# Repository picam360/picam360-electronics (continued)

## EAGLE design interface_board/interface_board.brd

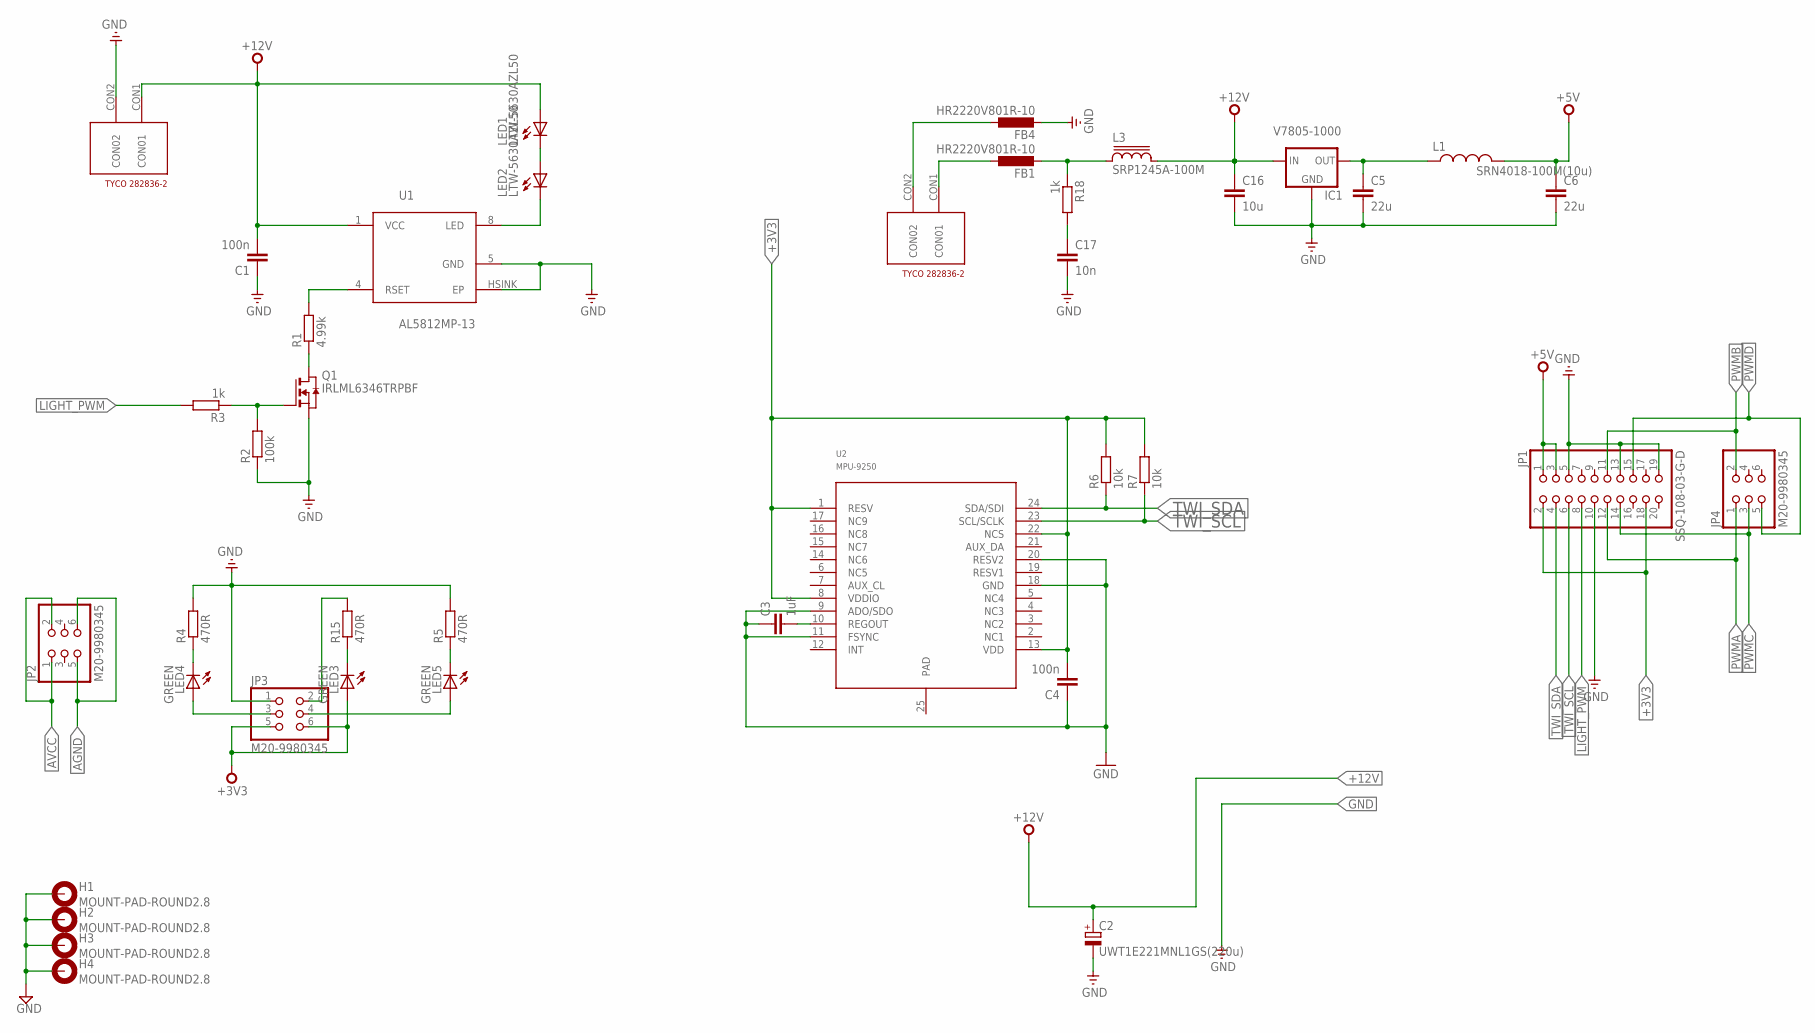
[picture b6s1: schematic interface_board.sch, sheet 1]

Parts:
C1, C4: 100n; C0402
C2: UWT1E221MNL1GS(220u); 153CLV-0810
C3: 1uF; C0402
C5, C6: 22u; C0603
C16: 10u; C0603
C17: 10n; C0402
FB1, FB4: HR2220V801R-10; L5650M
H1, H2, H3, H4: MOUNT-PAD-ROUND2.8; 2,8-PAD
IC1: V7805-1000; DIP_3PIN
JP1: SSQ-108-03-G-D; 2X10
JP2, JP3, JP4: M20-9980345; 2X03
L1: SRN4018-100M(10u); BOURNS-SRN4018
L3: SRP1245A-100M; SRP1250A
LED1, LED2: LTW-5630AZL50; LITEON-5630
LED3, LED4, LED5: GREEN; CHIP-LED0603
Q1: IRLML6346TRPBF; SOT23
R1: 4.99k; R0402
R2: 100k; R0402
R3, R18: 1k; R0402
R4, R5, R15: 470R; R0402
R6, R7: 10k; R0402
U1: AL5812MP-13; MSOP-8EP
U2: MPU-9250; LEAD-QFN24
U$2, U$4: 282836-2

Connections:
+3V3: C4.2, JP1.2, JP1.18, JP3.5, JP3.6, LED3.A, R6.2, R7.2, U2.1 (RESV), U2.8 (VDDIO), U2.13 (VDD), U2.22 (NCS); also elsewhere on the board
+5V: C6.1, JP1.1, JP1.3, L1.P$1 (1); also elsewhere on the board
+12V: C1.2, C2.+, C16.1, IC1.IN, L3.2, LED1.A1 (A), LED1.A2 (A), LED1.A3 (A), U1.1 (VCC), U$4.CON1 (CON01)
AGND: FB4.1, JP2.5, JP2.6, U$2.CON2 (CON02)
AVCC: FB1.1, JP2.1, JP2.2, U$2.CON1 (CON01)
GND: C1.1, C2.-, C3.1, C4.1, C5.2, C6.2, C16.2, C17.2, FB4.2, H1.B2,8, H2.B2,8, H3.B2,8, H4.B2,8, IC1.GND, JP1.5, JP1.10, JP1.13, JP1.19, JP3.1, Q1.2 (S), R2.1, R4.2, R5.2, U1.5 (GND), U1.HSINK (EP), U2.9 (ADO/SDO), U2.11 (FSYNC), U2.18 (GND), U2.20 (RESV2), U$4.CON2 (CON02); also elsewhere on the board
LIGHT_PWM: JP1.8, R3.2
unnamed: LED1.C1 (C), LED1.C2 (C), LED2.A1 (A), LED2.A2 (A), LED2.A3 (A)
unnamed: LED4.C, R4.1
unnamed: FB1.2, L3.1, R18.1
unnamed: C3.2, U2.10 (REGOUT)
unnamed: R1.2, U1.4 (RSET)
unnamed: Q1.3 (D), R1.1
unnamed: Q1.1 (G), R2.2, R3.1
unnamed: JP3.3, LED4.A
unnamed: LED2.C1 (C), LED2.C2 (C), U1.8 (LED)
unnamed: C5.1, IC1.OUT, L1.P$2 (2)
unnamed: JP3.4, LED5.A
unnamed: LED5.C, R5.1
unnamed: JP3.2, R15.2
unnamed: LED3.C, R15.1
unnamed: C17.1, R18.2
PWMA: JP1.12, JP4.1
PWMB: JP1.11, JP4.2
PWMC: JP1.14, JP4.3
PWMD: JP1.15, JP4.5
TWI_SCL: JP1.6, R7.1, U2.23 (SCL/SCLK)
TWI_SDA: JP1.4, R6.1, U2.24 (SDA/SDI)

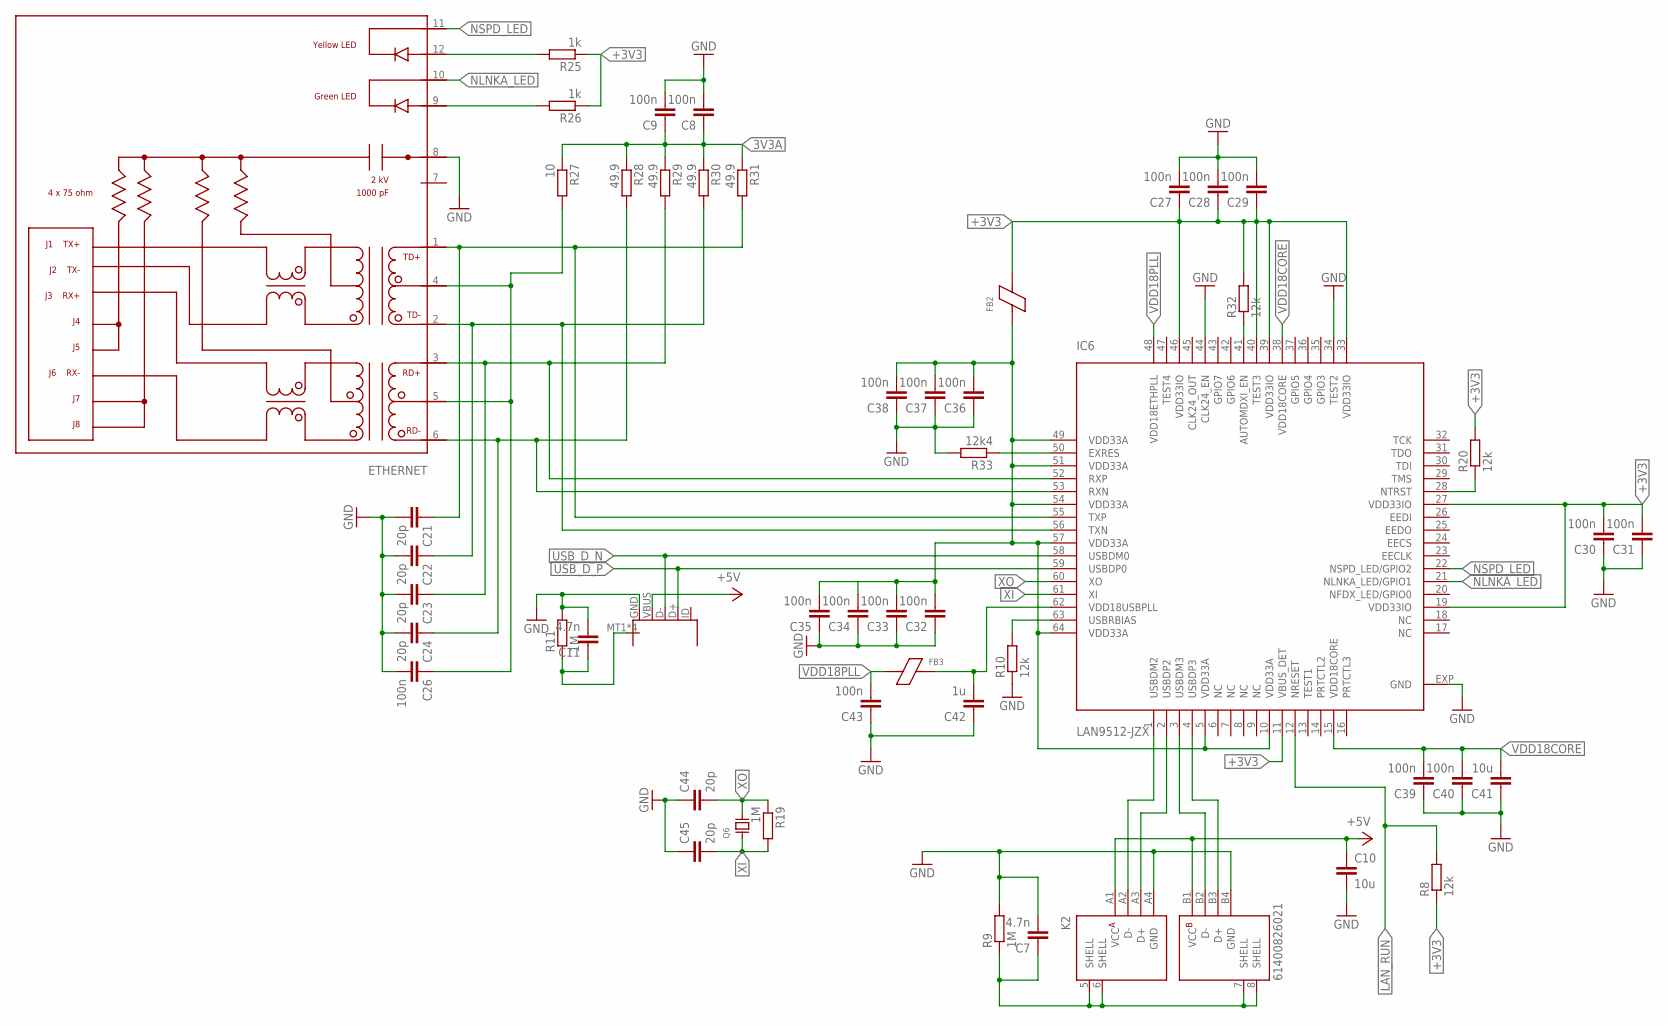
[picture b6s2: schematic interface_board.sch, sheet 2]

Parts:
C7, C11: 4.7n; C0402
C8, C9, C26, C27, C28, C29, C30, C31, C32, C33, C34, C35, C36, C37, C38, C39, C40, C43: 100n; C0402
C10, C41: 10u; C0603
C21, C22, C23, C24, C44, C45: 20p; C0402
C42: 1u; C0402
ETHERNET: HR911105A; RJ45
FB2, FB3: 742792022; C0805
IC6: LAN9512-JZX; QFN64-9X9
JP6: 10118192-0001LF; USB-MICRO
K2: 61400826021
Q6: FA-238 25.0000MB; CTS_32X25
R8, R10, R20, R32: 12k; R0402
R9, R11, R19: 1M; R0402
R25, R26: 1k; R0402
R27: 10; R0402
R28, R29, R30, R31: 49.9; R0402
R33: 12k4; R0402

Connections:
3V3A: C8.1, C9.1, C32.2, C33.2, C34.2, C35.2, C36.2, C37.2, C38.2, FB2.1, IC6.5 (VDD33A), IC6.10 (VDD33A), IC6.49 (VDD33A), IC6.51 (VDD33A), IC6.54 (VDD33A), IC6.57 (VDD33A), IC6.64 (VDD33A), R27.1, R28.1, R29.1, R30.1, R31.1
+3V3: C27.1, C28.1, C29.1, C30.2, C31.2, FB2.2, IC6.11 (VBUS_DET), IC6.19 (VDD33IO), IC6.27 (VDD33IO), IC6.33 (VDD33IO), IC6.39 (VDD33IO), IC6.40 (TEST3), IC6.46 (VDD33IO), R8.1, R20.2, R25.1, R26.1, R32.2; also elsewhere on the board
+5V: C10.1, JP6.VBUS, K2.A1 (VCC), K2.B1 (VCC); also elsewhere on the board
AVDD18PLL: C42.2, FB3.2, IC6.62 (VDD18USBPLL)
GND: C7.2, C8.2, C9.2, C10.2, C11.2, C21.2, C22.2, C23.2, C24.2, C26.2, C27.2, C28.2, C29.2, C30.1, C31.1, C32.1, C33.1, C34.1, C35.1, C36.1, C37.1, C38.1, C39.1, C40.1, C41.1, C42.1, C43.1, C44.1, C45.1, ETHERNET.8, IC6.34 (TEST2), IC6.44 (CLK24_EN), IC6.EXP (GND), JP6.GND, K2.A4 (GND), K2.B4 (GND), R9.2, R10.1, R11.2, R33.2; also elsewhere on the board
LAN_RUN: IC6.12 (NRESET), R8.2
unnamed: ETHERNET.12, R25.2
unnamed: ETHERNET.9, R26.2
unnamed: C26.1, ETHERNET.4, ETHERNET.5, R27.2
unnamed: IC6.63 (USBRBIAS), R10.2
unnamed: IC6.41 (AUTOMDXI_EN), R32.1
unnamed: IC6.50 (EXRES), R33.1
unnamed: IC6.28 (NTRST), R20.1
NLNKA_LED: ETHERNET.10, IC6.21 (NLNKA_LED/GPIO1)
NSPD_LED: ETHERNET.11, IC6.22 (NSPD_LED/GPIO2)
RX_N: C24.1, ETHERNET.6, IC6.53 (RXN), R28.2
RX_P: C23.1, ETHERNET.3, IC6.52 (RXP), R29.2
TX_N: C22.1, ETHERNET.2, IC6.56 (TXN), R30.2
TX_P: C21.1, ETHERNET.1, IC6.55 (TXP), R31.2
USB1_SHELL: C7.1, K2.5 (SHELL), K2.6 (SHELL), K2.7 (SHELL), K2.8 (SHELL), R9.1
USB2_SHELL: C11.1, JP6.MT1 (SHELL), JP6.MT2 (SHELL), JP6.P$1 (SHELL), JP6.P$2 (SHELL), R11.1
USBD2_N: IC6.1 (USBDM2), K2.A2 (D-)
USBD2_P: IC6.2 (USBDP2), K2.A3 (D+)
USBD3_N: IC6.3 (USBDM3), K2.B2 (D-)
USBD3_P: IC6.4 (USBDP3), K2.B3 (D+)
USB_D_N: IC6.58 (USBDM0), JP6.D-
USB_D_P: IC6.59 (USBDP0), JP6.D+
VDD18CORE: C39.2, C40.2, C41.2, IC6.15 (VDD18CORE), IC6.38 (VDD18CORE)
VDD18PLL: C43.2, FB3.1, IC6.48 (VDD18ETHPLL)
XI: C45.2, IC6.61 (XI), Q6.1 (X1), R19.2
XO: C44.2, IC6.60 (XO), Q6.3 (X2), R19.1

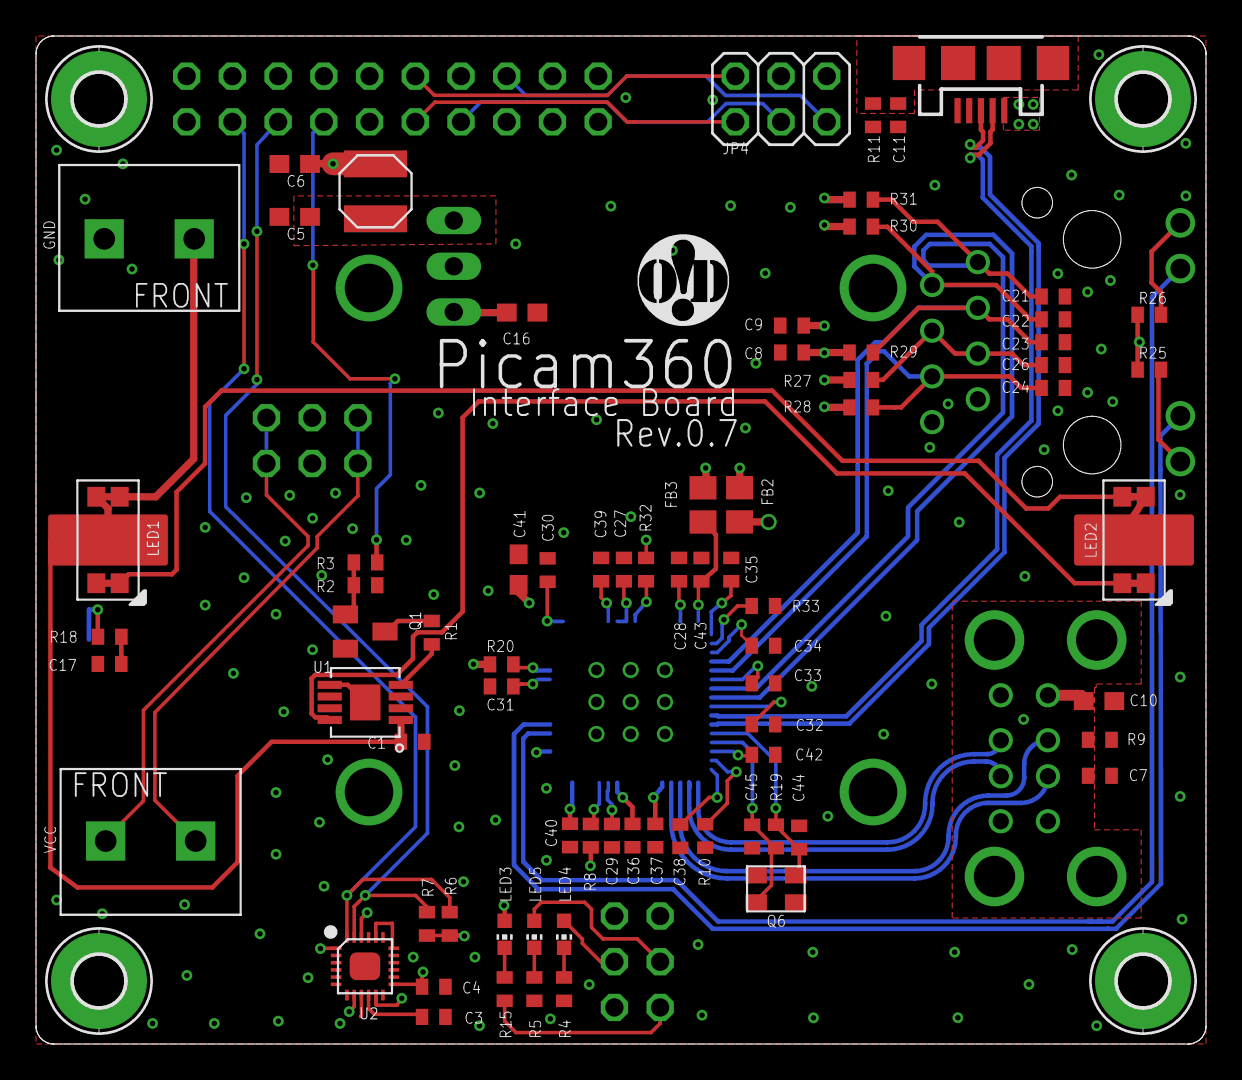
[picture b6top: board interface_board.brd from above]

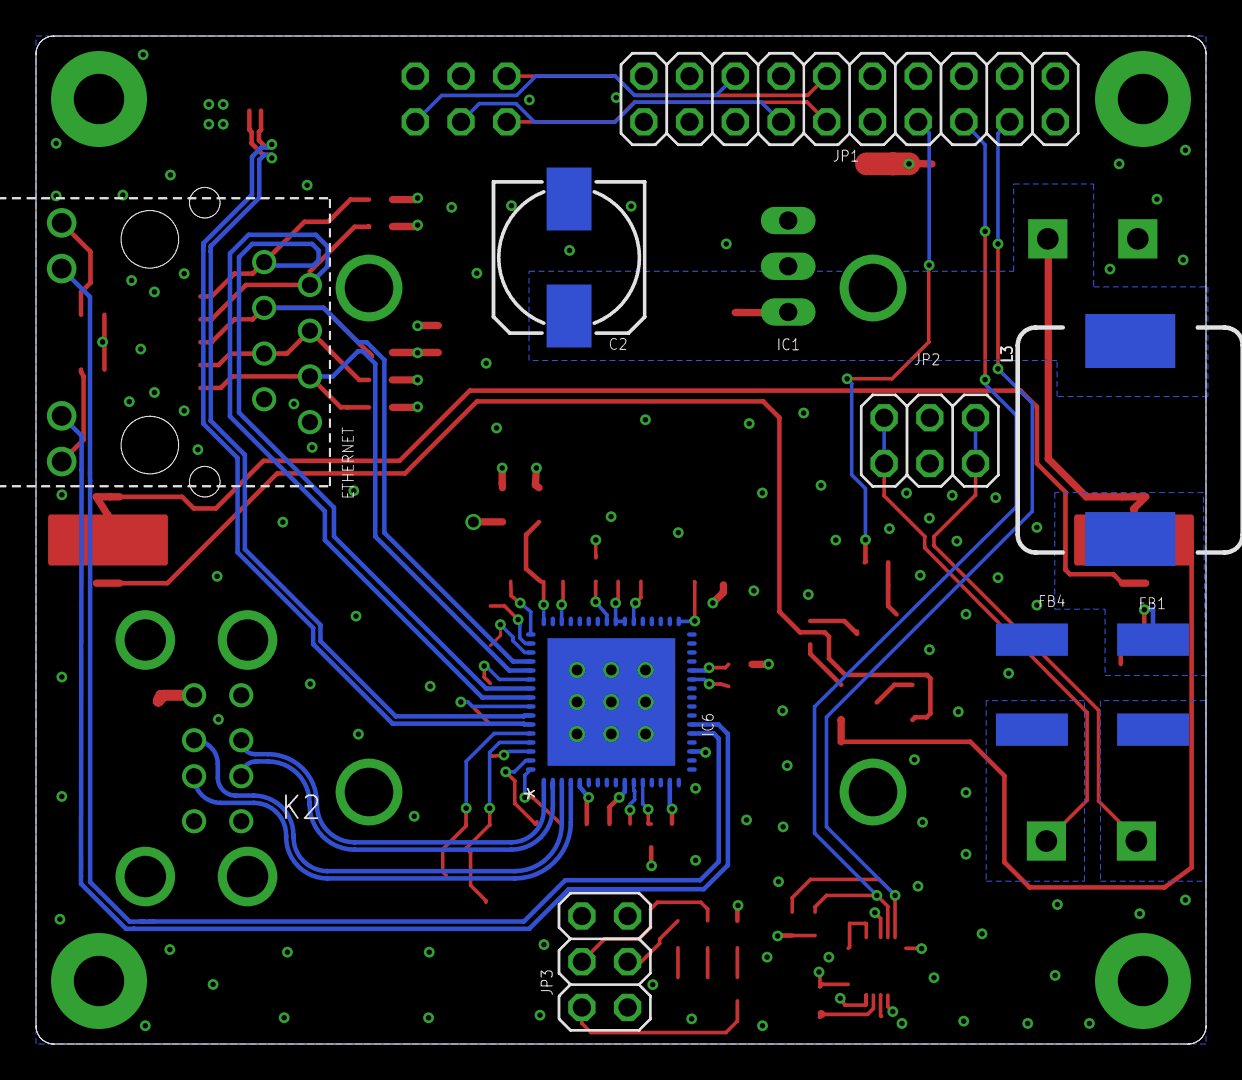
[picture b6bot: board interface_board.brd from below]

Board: 4 copper layers, 65.0 x 56.0 mm, 93 parts (12 on the bottom side), 56 nets.

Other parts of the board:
LOGO1: OHMYDIGIFAB_LOGO
U$1: TENDA_P200

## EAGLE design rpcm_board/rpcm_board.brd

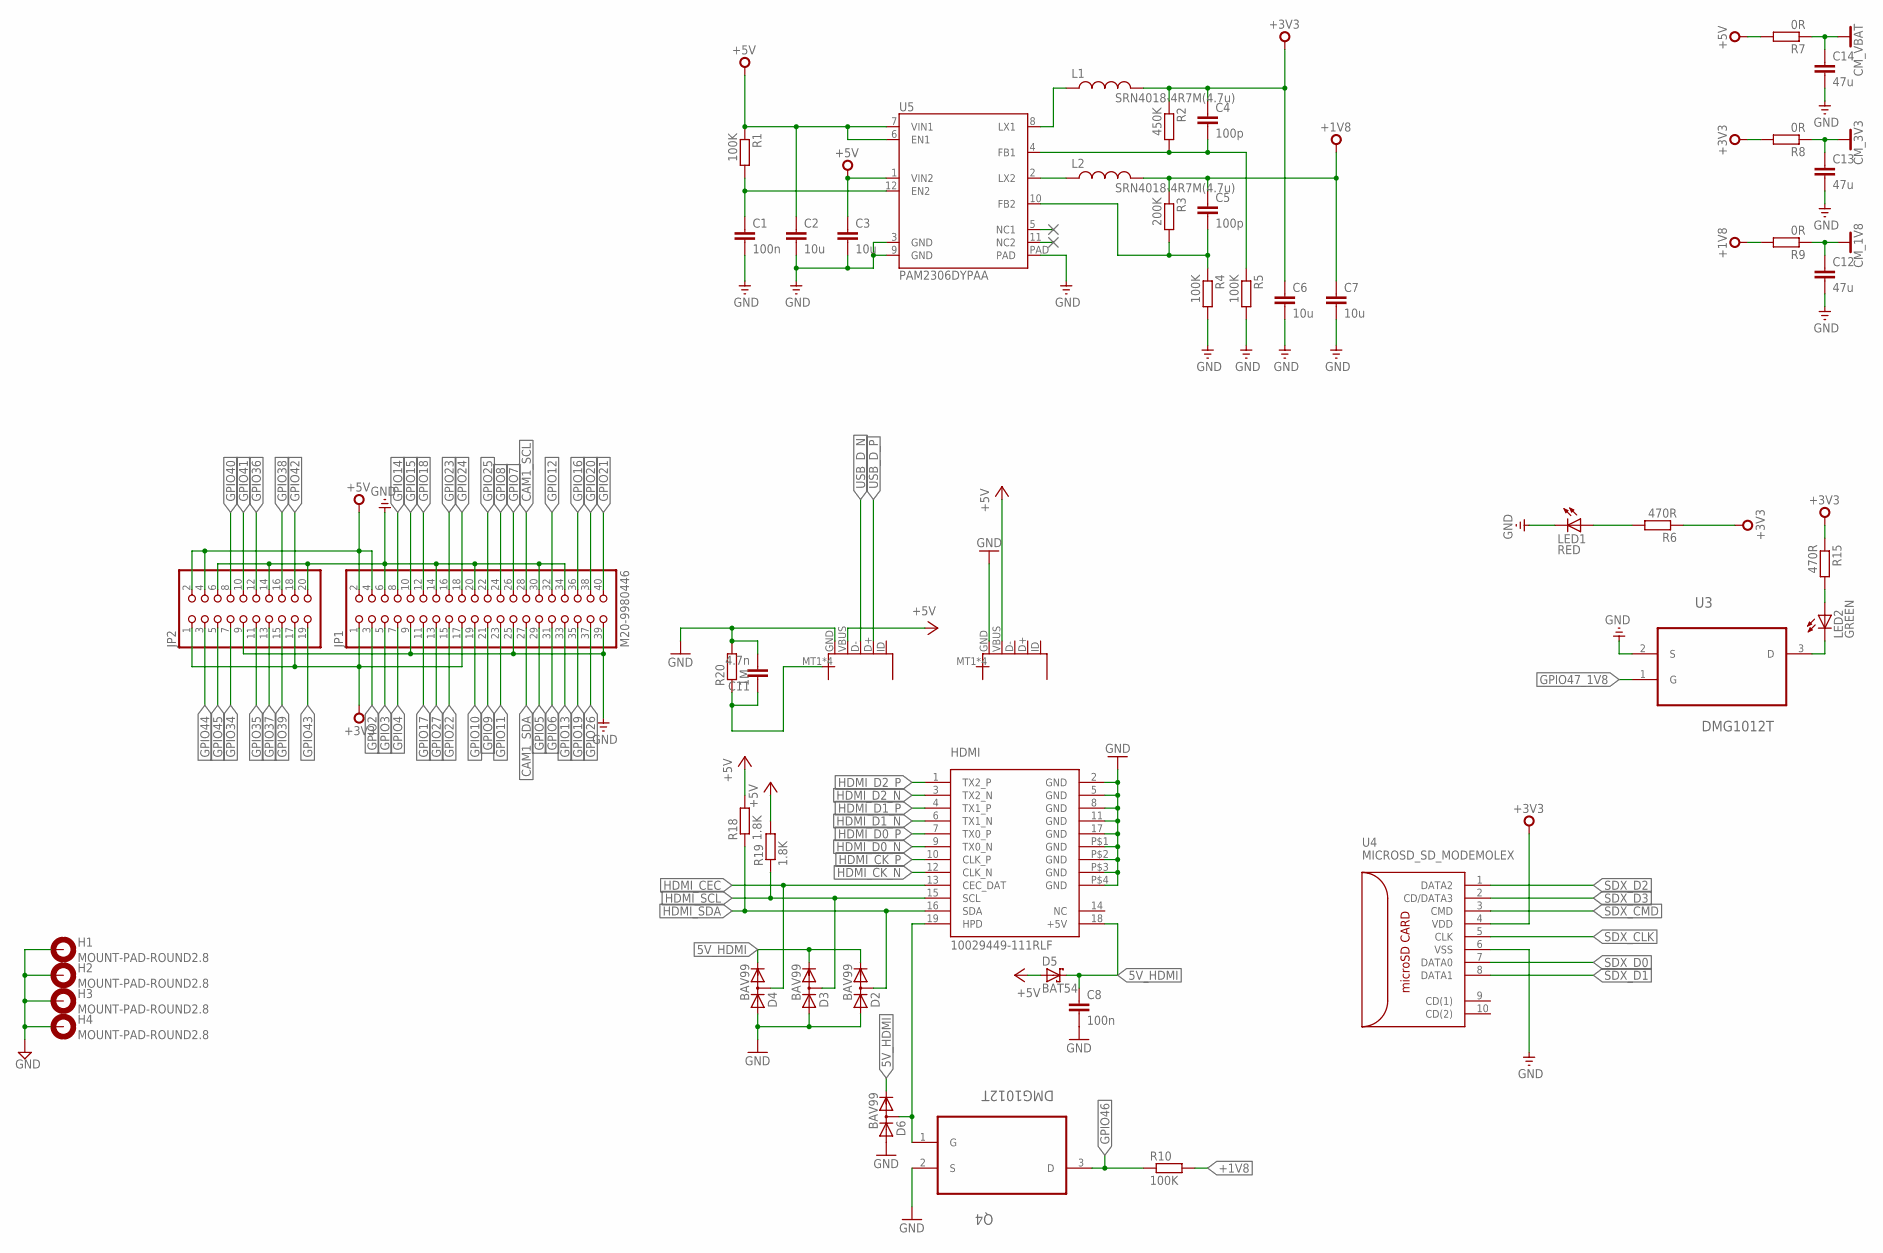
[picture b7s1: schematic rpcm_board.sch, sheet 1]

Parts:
C1, C8: 100n; C0402
C2, C3, C6, C7: 10u; C0805
C4, C5: 100p; C0402
C11: 4.7n; C0402
C12, C13, C14: 47u; C1206
D2, D3, D4, D6: BAV99; SOT23
D5: BAT54; SOT23
H1, H2, H3, H4: MOUNT-PAD-ROUND2.8; 2,8-PAD
HDMI: 10029449-111RLF; HDMI
JP1: M20-9980446; 2X20
JP2: PINHD-2X10; 2X10
JP3, JP6: USB-IDMICRO; USB-MICRO
L1, L2: SRN4018-4R7M(4.7u); BOURNS-SRN4018
LED1: RED; CHIP-LED0603
LED2: GREEN; CHIP-LED0603
Q4: DMG1012T; SOT523
R1, R4, R5, R10: 100K; R0402
R2: 450K; R0402
R3: 200K; R0402
R6, R15: 470R; R0402
R7, R8, R9: 0R; R0805
R18, R19: 1.8K; R0402
R20: 1M; R0402
U3: DMG1012T; SOT523
U4: MICROSD_SD_MODEMOLEX; MOLEX_1040310811
U5: PAM2306DYPAA; WDFN3X3-12L

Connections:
5V_HDMI: C8.1, D2.2 (C), D3.2 (C), D4.2 (C), D5.3 (C), D6.2 (C), HDMI.18 (+5V)
+1V8: C5.1, C7.1, L2.P$1 (1), R3.1, R9.2, R10.2
+3V3: C4.1, C6.1, JP1.1, JP1.17, JP2.1, JP2.17, L1.P$1 (1), R2.1, R6.1, R8.2, R15.1, U4.4 (VDD); also elsewhere on the board
+5V: C2.1, C3.1, D5.1 (A), JP1.2, JP1.4, JP2.2, JP2.4, JP3.VBUS, JP6.VBUS, R1.1, R7.2, R18.2, R19.2, U5.1 (VIN2), U5.6 (EN1), U5.7 (VIN1)
CAM1_SCL: JP1.28; also elsewhere on the board
CAM1_SDA: JP1.27; also elsewhere on the board
CM_1V8: C12.1, R9.1; also elsewhere on the board
CM_3V3: C13.1, R8.1; also elsewhere on the board
CM_VBAT: C14.1, R7.1; also elsewhere on the board
GND: C1.2, C2.2, C3.2, C6.2, C7.2, C8.2, C11.2, C12.2, C13.2, C14.2, D2.1 (A), D3.1 (A), D4.1 (A), D6.1 (A), H1.B2,8, H2.B2,8, H3.B2,8, H4.B2,8, HDMI.2 (GND), HDMI.5 (GND), HDMI.8 (GND), HDMI.11 (GND), HDMI.17 (GND), HDMI.P$1 (GND), HDMI.P$2 (GND), HDMI.P$3 (GND), HDMI.P$4 (GND), JP1.6, JP1.9, JP1.14, JP1.20, JP1.25, JP1.30, JP1.34, JP1.39, JP2.6, JP2.9, JP2.14, JP2.20, JP3.GND, JP6.GND, LED1.C, Q4.2 (S), R4.2, R5.2, R20.2, U3.2 (S), U4.6 (VSS), U5.3 (GND), U5.9 (GND), U5.PAD; also elsewhere on the board
GPIO2: JP1.3; also elsewhere on the board
GPIO3: JP1.5; also elsewhere on the board
GPIO4: JP1.7; also elsewhere on the board
GPIO5: JP1.29; also elsewhere on the board
GPIO6: JP1.31; also elsewhere on the board
GPIO7: JP1.26; also elsewhere on the board
GPIO8: JP1.24; also elsewhere on the board
GPIO9: JP1.21; also elsewhere on the board
GPIO10: JP1.19; also elsewhere on the board
GPIO11: JP1.23; also elsewhere on the board
GPIO12: JP1.32; also elsewhere on the board
GPIO13: JP1.33; also elsewhere on the board
GPIO14: JP1.8; also elsewhere on the board
GPIO15: JP1.10; also elsewhere on the board
GPIO16: JP1.36; also elsewhere on the board
GPIO17: JP1.11; also elsewhere on the board
GPIO18: JP1.12; also elsewhere on the board
GPIO19: JP1.35; also elsewhere on the board
GPIO20: JP1.38; also elsewhere on the board
GPIO21: JP1.40; also elsewhere on the board
GPIO22: JP1.15; also elsewhere on the board
GPIO23: JP1.16; also elsewhere on the board
GPIO24: JP1.18; also elsewhere on the board
GPIO25: JP1.22; also elsewhere on the board
GPIO26: JP1.37; also elsewhere on the board
GPIO27: JP1.13; also elsewhere on the board
GPIO34: JP2.7; also elsewhere on the board
GPIO35: JP2.11; also elsewhere on the board
GPIO36: JP2.12; also elsewhere on the board
GPIO37: JP2.13; also elsewhere on the board
GPIO38: JP2.16; also elsewhere on the board
GPIO39: JP2.15; also elsewhere on the board
GPIO40: JP2.8; also elsewhere on the board
GPIO41: JP2.10; also elsewhere on the board
GPIO42: JP2.18; also elsewhere on the board
GPIO43: JP2.19; also elsewhere on the board
GPIO44: JP2.3; also elsewhere on the board
GPIO45: JP2.5; also elsewhere on the board
GPIO46: Q4.3 (D), R10.1; also elsewhere on the board
GPIO47_1V8: U3.1 (G); also elsewhere on the board
HDMI_CEC: D4.3 (AC), HDMI.13 (CEC_DAT); also elsewhere on the board
HDMI_CK_N: HDMI.12 (CLK_N); also elsewhere on the board
HDMI_CK_P: HDMI.10 (CLK_P); also elsewhere on the board
HDMI_D0_N: HDMI.9 (TX0_N); also elsewhere on the board
HDMI_D0_P: HDMI.7 (TX0_P); also elsewhere on the board
HDMI_D1_N: HDMI.6 (TX1_N); also elsewhere on the board
HDMI_D1_P: HDMI.4 (TX1_P); also elsewhere on the board
HDMI_D2_N: HDMI.3 (TX2_N); also elsewhere on the board
HDMI_D2_P: HDMI.1 (TX2_P); also elsewhere on the board
HDMI_SCL: D3.3 (AC), HDMI.15 (SCL), R19.1; also elsewhere on the board
HDMI_SDA: D2.3 (AC), HDMI.16 (SDA), R18.1; also elsewhere on the board
unnamed: C1.1, R1.2, U5.12 (EN2)
unnamed: L1.P$2 (2), U5.8 (LX1)
unnamed: L2.P$2 (2), U5.2 (LX2)
unnamed: C4.2, R2.2, R5.1, U5.4 (FB1)
unnamed: LED1.A, R6.2
unnamed: C5.2, R3.2, R4.1, U5.10 (FB2)
unnamed: LED2.A, R15.2
unnamed: LED2.C, U3.3 (D)
unnamed: D6.3 (AC), HDMI.19 (HPD), Q4.1 (G)
SDX_CLK: U4.5 (CLK); also elsewhere on the board
SDX_CMD: U4.3 (CMD); also elsewhere on the board
SDX_D0: U4.7 (DATA0); also elsewhere on the board
SDX_D1: U4.8 (DATA1); also elsewhere on the board
SDX_D2: U4.1 (DATA2); also elsewhere on the board
SDX_D3: U4.2 (CD/DATA3); also elsewhere on the board
USB2_SHELL: C11.1, JP6.MT1 (SHELL), JP6.MT2 (SHELL), JP6.P$1 (SHELL), JP6.P$2 (SHELL), R20.1
USB_D_N: JP6.D-; also elsewhere on the board
USB_D_P: JP6.D+; also elsewhere on the board

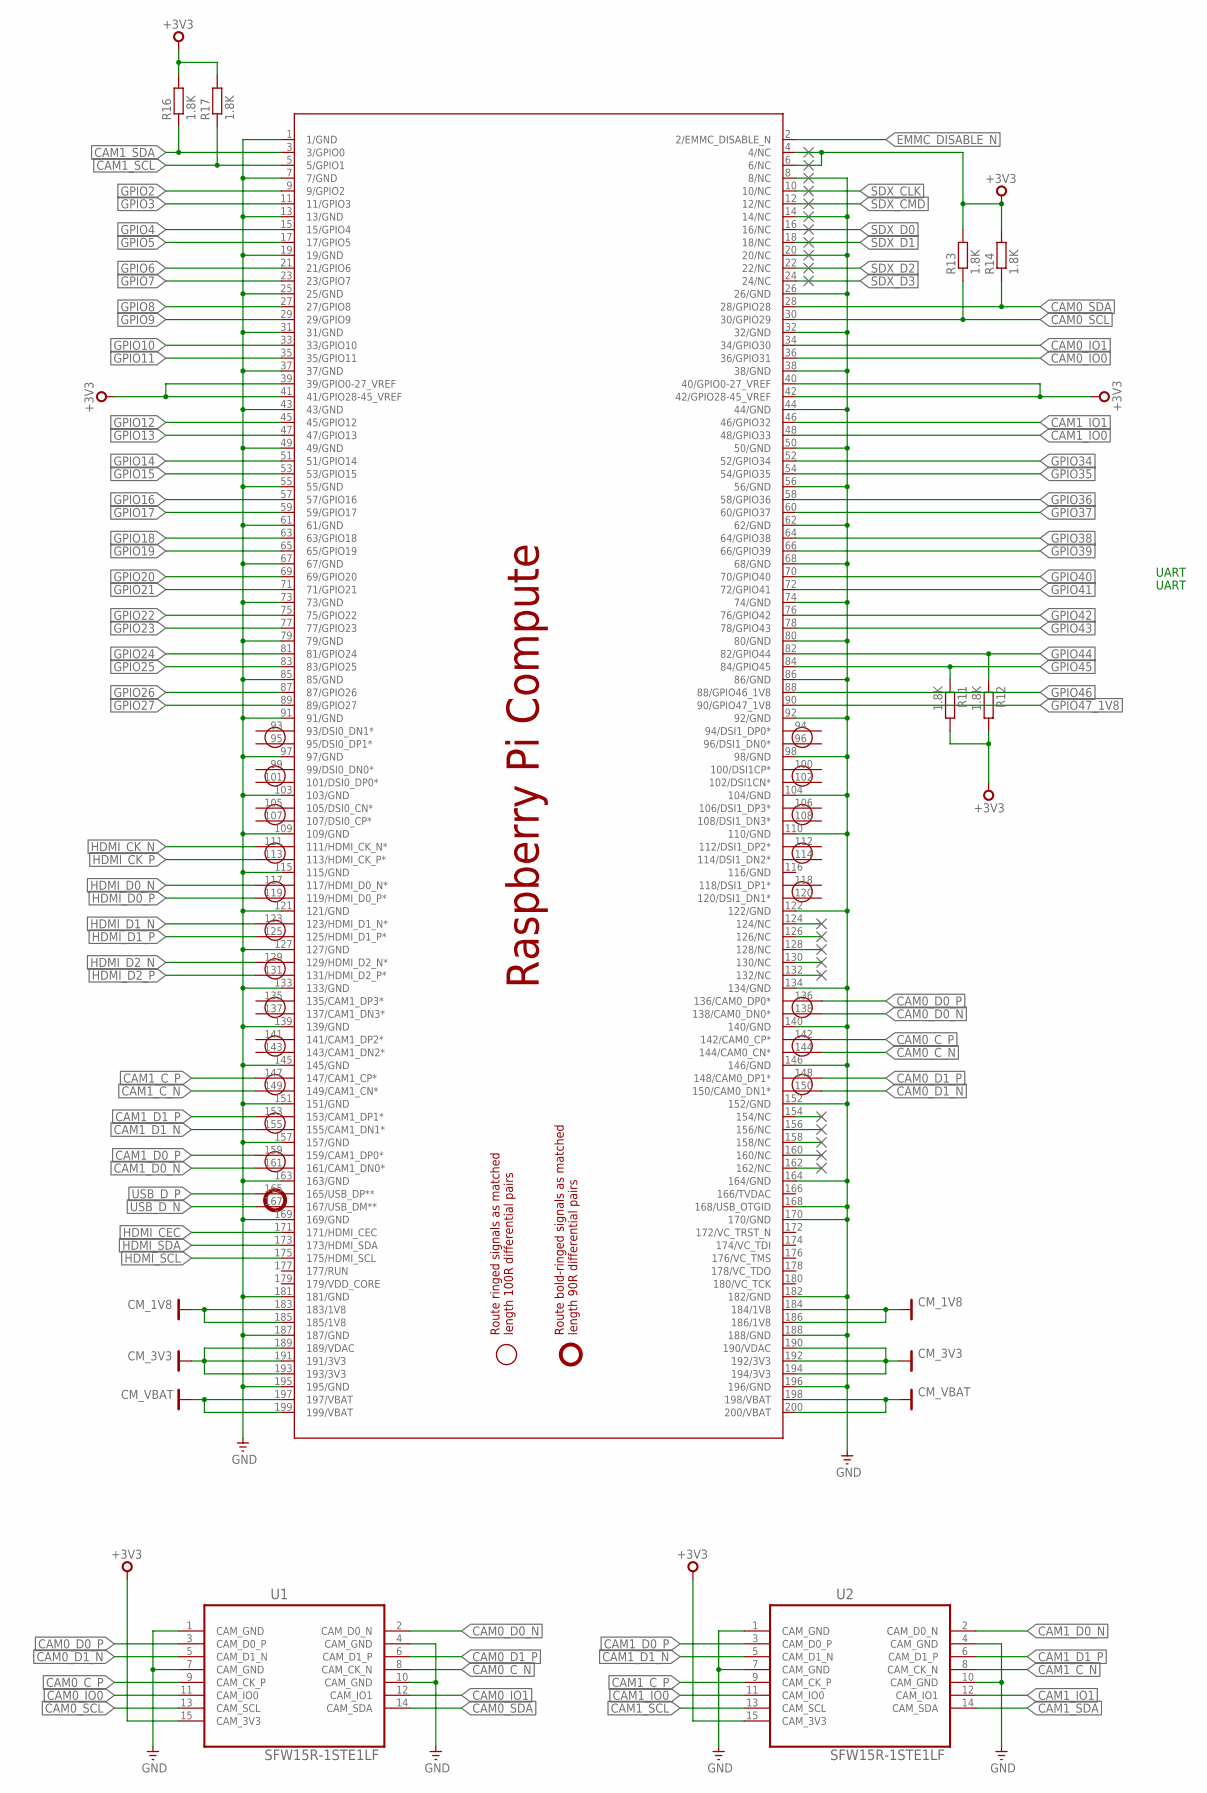
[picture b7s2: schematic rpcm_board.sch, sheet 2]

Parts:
PCB1: 1473005-4; RPI_COMPUTE
R11, R12, R13, R14, R16, R17: 1.8K; R0402
U1, U2: SFW15R-1STE1LF; RPI_CAMERA

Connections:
+3V3: PCB1.4 (4/NC), PCB1.6 (6/NC), PCB1.39 (39/GPIO0-27_VREF), PCB1.40 (40/GPIO0-27_VREF), PCB1.41 (41/GPIO28-45_VREF), PCB1.42 (42/GPIO28-45_VREF), R11.2, R12.2, R13.2, R14.2, R16.2, R17.2, U1.15 (CAM_3V3), U2.15 (CAM_3V3); also elsewhere on the board
CAM0_C_N: PCB1.144 (144/CAM0_CN*), U1.8 (CAM_CK_N)
CAM0_C_P: PCB1.142 (142/CAM0_CP*), U1.9 (CAM_CK_P)
CAM0_D0_N: PCB1.138 (138/CAM0_DN0*), U1.2 (CAM_D0_N)
CAM0_D0_P: PCB1.136 (136/CAM0_DP0*), U1.3 (CAM_D0_P)
CAM0_D1_N: PCB1.150 (150/CAM0_DN1*), U1.5 (CAM_D1_N)
CAM0_D1_P: PCB1.148 (148/CAM0_DP1*), U1.6 (CAM_D1_P)
CAM0_IO0: PCB1.36 (36/GPIO31), U1.11 (CAM_IO0)
CAM0_IO1: PCB1.34 (34/GPIO30), U1.12 (CAM_IO1)
CAM0_SCL: PCB1.30 (30/GPIO29), R13.1, U1.13 (CAM_SCL)
CAM0_SDA: PCB1.28 (28/GPIO28), R14.1, U1.14 (CAM_SDA)
CAM1_C_N: PCB1.149 (149/CAM1_CN*), U2.8 (CAM_CK_N)
CAM1_C_P: PCB1.147 (147/CAM1_CP*), U2.9 (CAM_CK_P)
CAM1_D0_N: PCB1.161 (161/CAM1_DN0*), U2.2 (CAM_D0_N)
CAM1_D0_P: PCB1.159 (159/CAM1_DP0*), U2.3 (CAM_D0_P)
CAM1_D1_N: PCB1.155 (155/CAM1_DN1*), U2.5 (CAM_D1_N)
CAM1_D1_P: PCB1.153 (153/CAM1_DP1*), U2.6 (CAM_D1_P)
CAM1_IO0: PCB1.48 (48/GPIO33), U2.11 (CAM_IO0)
CAM1_IO1: PCB1.46 (46/GPIO32), U2.12 (CAM_IO1)
CAM1_SCL: PCB1.5 (5/GPIO1), R17.1, U2.13 (CAM_SCL); also elsewhere on the board
CAM1_SDA: PCB1.3 (3/GPIO0), R16.1, U2.14 (CAM_SDA); also elsewhere on the board
CM_1V8: PCB1.183 (183/1V8), PCB1.184 (184/1V8), PCB1.185 (185/1V8), PCB1.186 (186/1V8); also elsewhere on the board
CM_3V3: PCB1.189 (189/VDAC), PCB1.190 (190/VDAC), PCB1.191 (191/3V3), PCB1.192 (192/3V3), PCB1.193 (193/3V3), PCB1.194 (194/3V3); also elsewhere on the board
CM_VBAT: PCB1.197 (197/VBAT), PCB1.198 (198/VBAT), PCB1.199 (199/VBAT), PCB1.200 (200/VBAT); also elsewhere on the board
EMMC_DISABLE_N: PCB1.2 (2/EMMC_DISABLE_N)
GND: PCB1.1 (1/GND), PCB1.7 (7/GND), PCB1.8 (8/NC), PCB1.13 (13/GND), PCB1.14 (14/NC), PCB1.19 (19/GND), PCB1.20 (20/NC), PCB1.25 (25/GND), PCB1.26 (26/GND), PCB1.31 (31/GND), PCB1.32 (32/GND), PCB1.37 (37/GND), PCB1.38 (38/GND), PCB1.43 (43/GND), PCB1.44 (44/GND), PCB1.49 (49/GND), PCB1.50 (50/GND), PCB1.55 (55/GND), PCB1.56 (56/GND), PCB1.61 (61/GND), PCB1.62 (62/GND), PCB1.67 (67/GND), PCB1.68 (68/GND), PCB1.73 (73/GND), PCB1.74 (74/GND), PCB1.79 (79/GND), PCB1.80 (80/GND), PCB1.85 (85/GND), PCB1.86 (86/GND), PCB1.91 (91/GND), PCB1.92 (92/GND), PCB1.97 (97/GND), PCB1.98 (98/GND), PCB1.103 (103/GND), PCB1.104 (104/GND), PCB1.109 (109/GND), PCB1.110 (110/GND), PCB1.115 (115/GND), PCB1.121 (121/GND), PCB1.122 (122/GND), PCB1.127 (127/GND), PCB1.133 (133/GND), PCB1.134 (134/GND), PCB1.139 (139/GND), PCB1.140 (140/GND), PCB1.145 (145/GND), PCB1.146 (146/GND), PCB1.151 (151/GND), PCB1.152 (152/GND), PCB1.157 (157/GND), PCB1.163 (163/GND), PCB1.164 (164/GND), PCB1.168 (168/USB_OTGID), PCB1.169 (169/GND), PCB1.170 (170/GND), PCB1.181 (181/GND), PCB1.182 (182/GND), PCB1.187 (187/GND), PCB1.188 (188/GND), PCB1.195 (195/GND), PCB1.196 (196/GND), U1.1 (CAM_GND), U1.4 (CAM_GND), U1.7 (CAM_GND), U1.10 (CAM_GND), U2.1 (CAM_GND), U2.4 (CAM_GND), U2.7 (CAM_GND), U2.10 (CAM_GND); also elsewhere on the board
GPIO2: PCB1.9 (9/GPIO2); also elsewhere on the board
GPIO3: PCB1.11 (11/GPIO3); also elsewhere on the board
GPIO4: PCB1.15 (15/GPIO4); also elsewhere on the board
GPIO5: PCB1.17 (17/GPIO5); also elsewhere on the board
GPIO6: PCB1.21 (21/GPIO6); also elsewhere on the board
GPIO7: PCB1.23 (23/GPIO7); also elsewhere on the board
GPIO8: PCB1.27 (27/GPIO8); also elsewhere on the board
GPIO9: PCB1.29 (29/GPIO9); also elsewhere on the board
GPIO10: PCB1.33 (33/GPIO10); also elsewhere on the board
GPIO11: PCB1.35 (35/GPIO11); also elsewhere on the board
GPIO12: PCB1.45 (45/GPIO12); also elsewhere on the board
GPIO13: PCB1.47 (47/GPIO13); also elsewhere on the board
GPIO14: PCB1.51 (51/GPIO14); also elsewhere on the board
GPIO15: PCB1.53 (53/GPIO15); also elsewhere on the board
GPIO16: PCB1.57 (57/GPIO16); also elsewhere on the board
GPIO17: PCB1.59 (59/GPIO17); also elsewhere on the board
GPIO18: PCB1.63 (63/GPIO18); also elsewhere on the board
GPIO19: PCB1.65 (65/GPIO19); also elsewhere on the board
GPIO20: PCB1.69 (69/GPIO20); also elsewhere on the board
GPIO21: PCB1.71 (71/GPIO21); also elsewhere on the board
GPIO22: PCB1.75 (75/GPIO22); also elsewhere on the board
GPIO23: PCB1.77 (77/GPIO23); also elsewhere on the board
GPIO24: PCB1.81 (81/GPIO24); also elsewhere on the board
GPIO25: PCB1.83 (83/GPIO25); also elsewhere on the board
GPIO26: PCB1.87 (87/GPIO26); also elsewhere on the board
GPIO27: PCB1.89 (89/GPIO27); also elsewhere on the board
GPIO34: PCB1.52 (52/GPIO34); also elsewhere on the board
GPIO35: PCB1.54 (54/GPIO35); also elsewhere on the board
GPIO36: PCB1.58 (58/GPIO36); also elsewhere on the board
GPIO37: PCB1.60 (60/GPIO37); also elsewhere on the board
GPIO38: PCB1.64 (64/GPIO38); also elsewhere on the board
GPIO39: PCB1.66 (66/GPIO39); also elsewhere on the board
GPIO40: PCB1.70 (70/GPIO40); also elsewhere on the board
GPIO41: PCB1.72 (72/GPIO41); also elsewhere on the board
GPIO42: PCB1.76 (76/GPIO42); also elsewhere on the board
GPIO43: PCB1.78 (78/GPIO43); also elsewhere on the board
GPIO44: PCB1.82 (82/GPIO44), R12.1; also elsewhere on the board
GPIO45: PCB1.84 (84/GPIO45), R11.1; also elsewhere on the board
GPIO46: PCB1.88 (88/GPIO46_1V8); also elsewhere on the board
GPIO47_1V8: PCB1.90 (90/GPIO47_1V8); also elsewhere on the board
HDMI_CEC: PCB1.171 (171/HDMI_CEC); also elsewhere on the board
HDMI_CK_N: PCB1.111 (111/HDMI_CK_N*); also elsewhere on the board
HDMI_CK_P: PCB1.113 (113/HDMI_CK_P*); also elsewhere on the board
HDMI_D0_N: PCB1.117 (117/HDMI_D0_N*); also elsewhere on the board
HDMI_D0_P: PCB1.119 (119/HDMI_D0_P*); also elsewhere on the board
HDMI_D1_N: PCB1.123 (123/HDMI_D1_N*); also elsewhere on the board
HDMI_D1_P: PCB1.125 (125/HDMI_D1_P*); also elsewhere on the board
HDMI_D2_N: PCB1.129 (129/HDMI_D2_N*); also elsewhere on the board
HDMI_D2_P: PCB1.131 (131/HDMI_D2_P*); also elsewhere on the board
HDMI_SCL: PCB1.175 (175/HDMI_SCL); also elsewhere on the board
HDMI_SDA: PCB1.173 (173/HDMI_SDA); also elsewhere on the board
SDX_CLK: PCB1.10 (10/NC); also elsewhere on the board
SDX_CMD: PCB1.12 (12/NC); also elsewhere on the board
SDX_D0: PCB1.16 (16/NC); also elsewhere on the board
SDX_D1: PCB1.18 (18/NC); also elsewhere on the board
SDX_D2: PCB1.22 (22/NC); also elsewhere on the board
SDX_D3: PCB1.24 (24/NC); also elsewhere on the board
USB_D_N: PCB1.167 (167/USB_DM**); also elsewhere on the board
USB_D_P: PCB1.165 (165/USB_DP**); also elsewhere on the board

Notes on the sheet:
UART
